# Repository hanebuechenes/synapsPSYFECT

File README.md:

# synapsPSYFECT

**synapsPSYFECT** is a high-end, 6-sheet multi-stage analog/hybrid FX Eurorack module designed for deep signal manipulation, multi-effect cross-modulation, and active spatial shaping.

The module combines a 4-Stage Vactrol Phaser, a Dual PT2399 Delay, and an LM13700-based Quadrature Frequency Shifter/Ring Modulator, all interconnected through a flexible active summing cross-modulation matrix.

---

## Technical Features & Architecture

* **Multi-Stage Architecture:** 6 dedicated schematic sheets covering Power, CV Buffering, Matrix Summing, Phaser, Dual Delay, and Frequency Shifter.
* **Active Input Buffering & Summing Matrix (`U12C`/`U4`/`U5`):** Dedicated TL074 operational amplifier buffers for all audio inputs and cross-modulation feedback paths to prevent crosstalk and signal bleed.
* **4-Stage Vactrol Phaser (`U7`/`U6`, `U8`, `U10`, `U11`):** All-pass filter architecture utilizing VTL5C vactrols for smooth, organic, analog phase shifting with CV control (`PHASER_CV`) and manual resonance feedback (`RES_POT1`).
* **Dual PT2399 Delay (`U12`/`U13`):** Two PT2399 ICs with voltage-controlled delay time (`DELAY_TIME_CV` via `Q2`/`Q3`) and transistor-shunt feedback modulation (`FEEDBACK_CV` via `Q4`).
* **LM13700 Frequency Shifter (`U14`/`U5`/`U9`):** Quadrature carrier oscillator generating sine/cosine phases (`CARRIER_SIN`/`CARRIER_COS`) driving a dual-OTA LM13700 for true frequency shifting and ring modulation (`SHIFT_CV`).
* **BOM & Component Standards:** SMD implementation (0603 / 0805 passives). **Strictly 0% Tantalum capacitors**, relying on NP0/C0G MLCCs for frequency-critical audio paths, X7R/X5R MLCCs, and SMD Aluminum Electrolytic capacitors for power rail filter banks.

---

## Module Specifications

| Specification | Parameter / Value |
| :--- | :--- |
| **Format** | Eurorack Synthesis Module |
| **Power Supply** | $\pm 12\text{VDC}$ Eurorack Standard Bus |
| **Internal Rails** | $+12\text{VA}$, $-12\text{VA}$, $+5\text{V}$, $+3.3\text{V}$, $+1.65\text{V\_REF}$ |
| **Input CV Protection** | $100\text{k}\Omega$ series resistors with 1N4148W clamping diodes & TL074 buffer stages |
| **Passive Component Sizes** | SMD 0603 (resistors & decoupling), SMD 0805 / 1206 (capacitors) |
| **IC Footprints** | SOIC-14, SOP-16, SOIC-16, SOT-223 |

---

## Signal Flow Overview

```
                          +------------------------+
                          |  CV Inputs (Protected) |
                          +-----------+------------+
                                      |
                                      v
  [AUDIO_IN] ---> [Input Buffer] ---> ( Matrix / Routing ) ---> [Phaser Stage (VTL5C)]
                       |                     |             ---> [Dual PT2399 Delay]
                       |                     |             ---> [LM13700 Freq Shifter]
                       v                     v
                 +-------------------------------+
                 | Active Cross-Mod Summing      | ---> [Audio Output]
                 | & Dry/Wet Mix (TL074)         |
                 +-------------------------------+
```

---

## Procurement & Assembly Notes

* **Capacitor Types:** 
  * Use **NP0/C0G** dielectrics for $10\text{nF}$ capacitors in the Phaser (`C13`–`C16`) and Quadrature Oscillator (`C35`–`C36`) to minimize temperature drift and microphonics.
  * Use **X7R/X5R** for all $100\text{nF}$ decoupling capacitors (`C39`–`C48` placed directly at TL074 power pins 4 & 11).
* **SMD Hand-Soldering:** 0603/0805 components chosen for manageable DIY manual assembly or automated SMT placement (JLCPCB compatible).

---

## Repository Structure

```
├── hardware/              # KiCad project files (.kicad_pro, .kicad_sch, .kicad_pcb)
├── bom/                   # Bill of Materials (BOM exports / iBOM)
├── docs/                  # Gerber files, schematic PDFs, and design notes
├── .gitignore             # KiCad temporary & build file exclusions
└── README.md              # Project documentation
```

---

## License

Hardware open-source project created by **hanebuechenes / synaps**. Distributed under the CERN-OHL-P (Permissive) or MIT License.

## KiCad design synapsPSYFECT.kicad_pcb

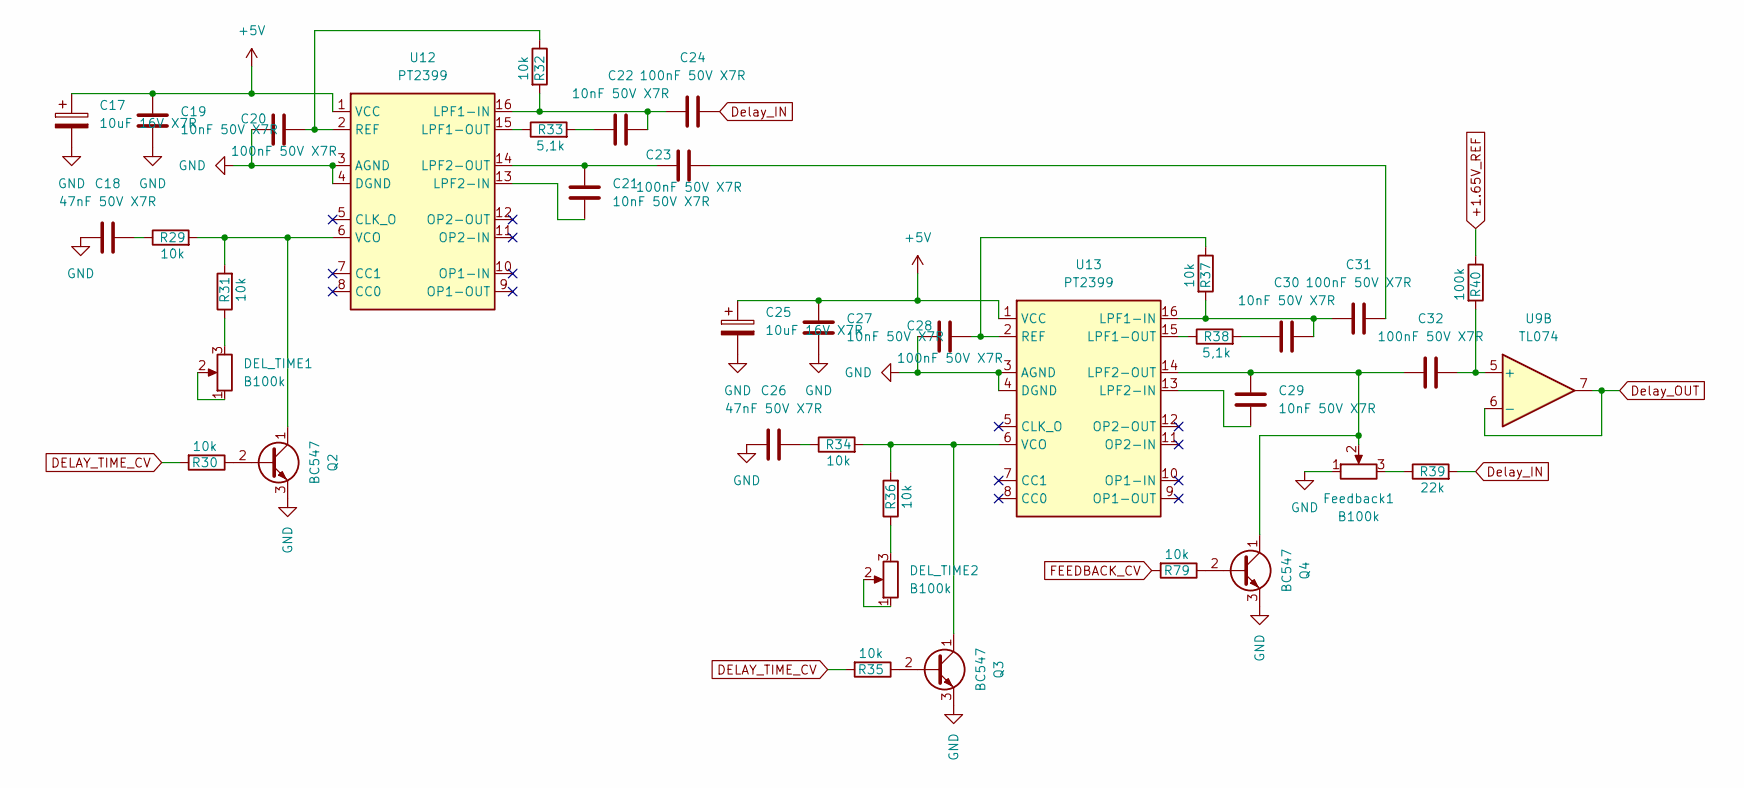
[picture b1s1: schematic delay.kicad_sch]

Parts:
C17, C25: 10uF 16V X7R; C_0805_2012Metric_Pad1.18x1.45mm_HandSolder
C18, C26: 47nF 50V X7R; C_0603_1608Metric_Pad1.08x0.95mm_HandSolder
C19, C21, C22, C27, C29, C30: 10nF 50V X7R; C_0603_1608Metric_Pad1.08x0.95mm_HandSolder
C20, C23, C24, C28, C31, C32: 100nF 50V X7R; C_0603_1608Metric_Pad1.08x0.95mm_HandSolder
DEL_TIME1, DEL_TIME2: B100k; Potentiometer_Alps_RK09K_Single_Vertical
Feedback1: B100k; Potentiometer_Alps_RK09K_Single_Vertical
Q2, Q3, Q4: BC547; SOT-23-3
R29, R30, R31, R32, R34, R35, R36, R37, R79: 10k; R_0603_1608Metric_Pad0.98x0.95mm_HandSolder
R33, R38: 5,1k; R_0603_1608Metric_Pad0.98x0.95mm_HandSolder
R39: 22k; R_0603_1608Metric_Pad0.98x0.95mm_HandSolder
R40: 100k; R_0603_1608Metric_Pad0.98x0.95mm_HandSolder
U9: TL074; SOIC-14_3.9x8.7mm_P1.27mm
U12, U13: PT2399; SOP-16_4.4x10.4mm_P1.27mm

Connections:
+1.65V_REF: R40.1; also elsewhere on the board
+5V: C17.1, C19.2, C25.1, C27.2, U12.1 (VCC), U13.1 (VCC); also elsewhere on the board
DELAY_TIME_CV: R30.2, R35.2; also elsewhere on the board
Delay_IN: C24.1, R39.2; also elsewhere on the board
Delay_OUT: U9.6 (-), U9.7; also elsewhere on the board
FEEDBACK_CV: R79.2; also elsewhere on the board
GND: C17.2, C18.1, C19.1, C20.1, C25.2, C26.1, C27.1, C28.1, Feedback1.1, Q2.3 (E), Q3.3 (E), Q4.3 (E), U12.3 (AGND), U12.4 (DGND), U13.3 (AGND), U13.4 (DGND); also elsewhere on the board
unnamed: C18.2, R29.1
unnamed: C22.1, R33.2
unnamed: C23.2, C31.1
unnamed: C26.2, R34.1
unnamed: C30.1, R38.2
unnamed: DEL_TIME1.1, DEL_TIME1.2
unnamed: DEL_TIME1.3, R31.1
unnamed: DEL_TIME2.1, DEL_TIME2.2
unnamed: DEL_TIME2.3, R36.1
unnamed: Feedback1.3, R39.1
unnamed: Q2.2 (B), R30.1
unnamed: Q2.1 (C), R29.2, R31.2, U12.6 (VCO)
unnamed: Q3.2 (B), R35.1
unnamed: Q3.1 (C), R34.2, R36.2, U13.6 (VCO)
unnamed: Q4.2 (B), R79.1
unnamed: C29.2, C32.2, Feedback1.2, Q4.1 (C), U13.14 (LPF2-OUT)
unnamed: C32.1, R40.2, U9.5 (+)
unnamed: C22.2, C24.2, R32.2, U12.16 (LPF1-IN)
unnamed: R33.1, U12.15 (LPF1-OUT)
unnamed: C21.1, U12.13 (LPF2-IN)
unnamed: C21.2, C23.1, U12.14 (LPF2-OUT)
unnamed: C20.2, R32.1, U12.2 (REF)
unnamed: C30.2, C31.2, R37.2, U13.16 (LPF1-IN)
unnamed: R38.1, U13.15 (LPF1-OUT)
unnamed: C29.1, U13.13 (LPF2-IN)
unnamed: C28.2, R37.1, U13.2 (REF)

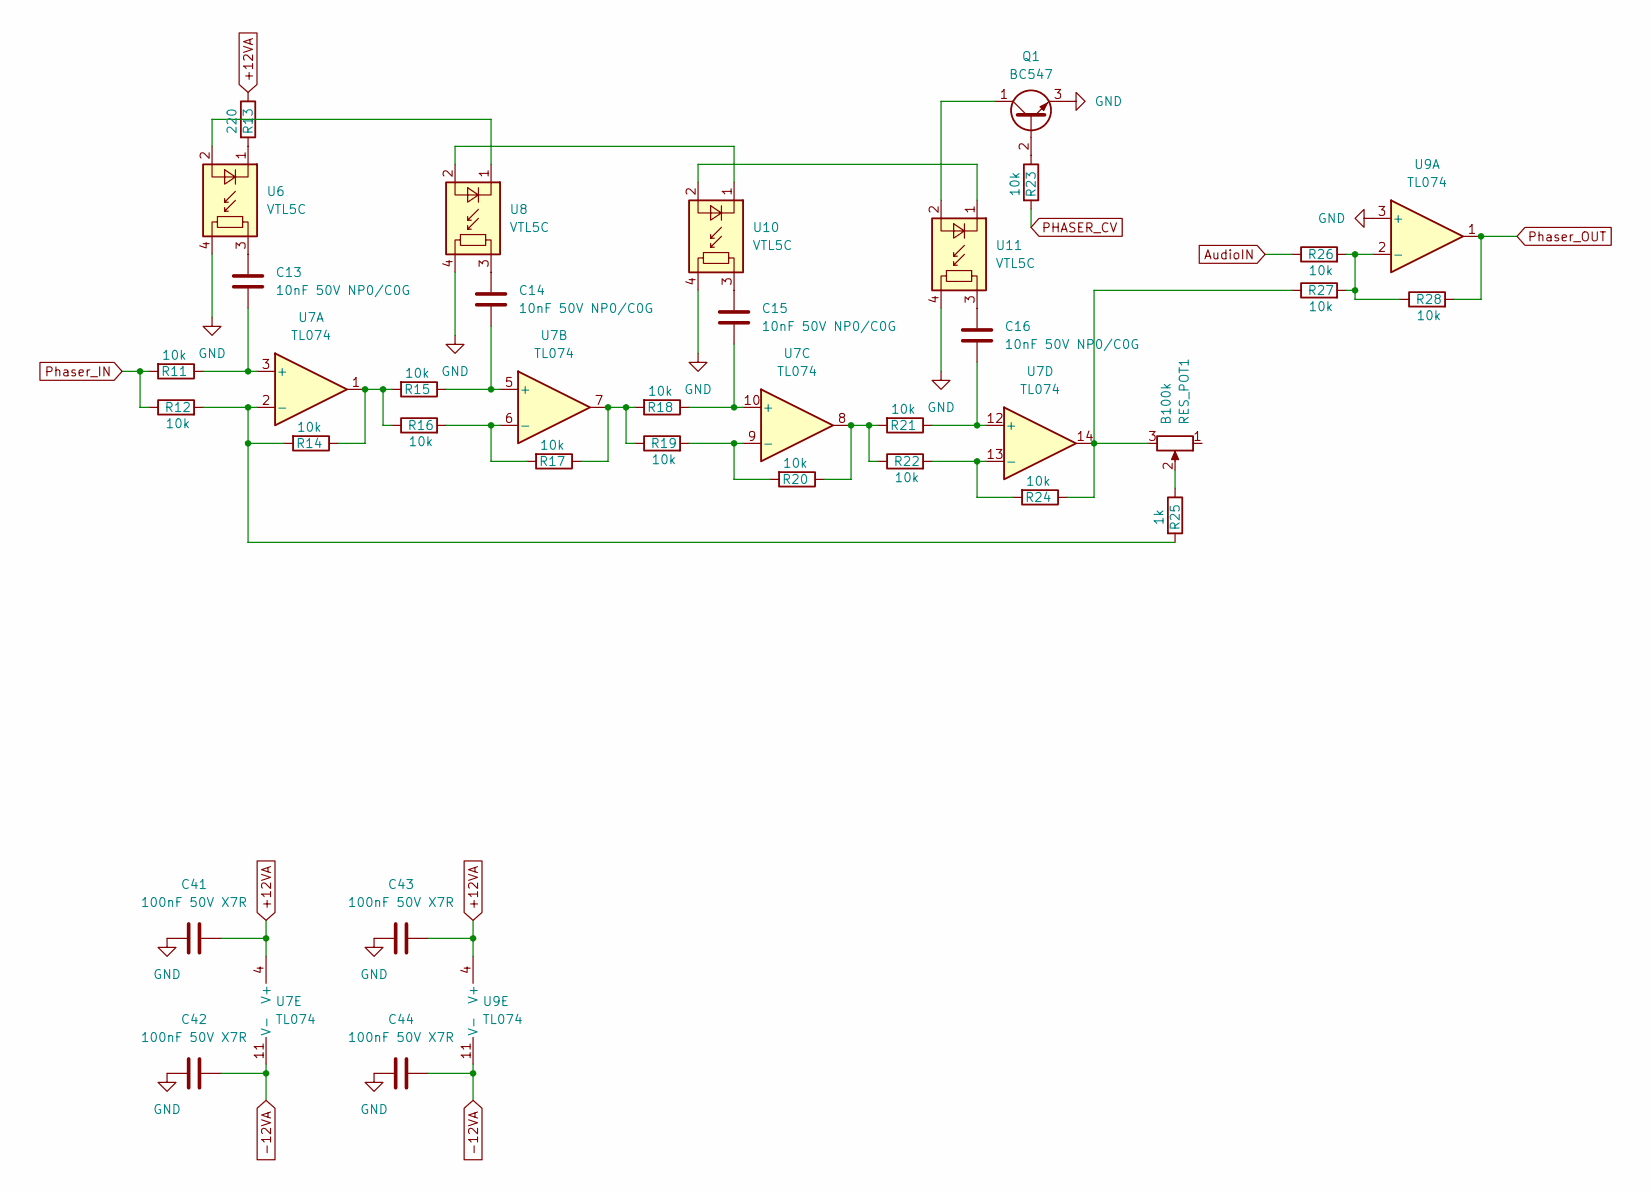
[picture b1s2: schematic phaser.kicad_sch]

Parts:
C13, C14, C15, C16: 10nF 50V NP0/C0G; C_0603_1608Metric_Pad1.08x0.95mm_HandSolder
C41, C42, C43, C44: 100nF 50V X7R; C_0603_1608Metric_Pad1.08x0.95mm_HandSolder
Q1: BC547; SOT-23-3
R11, R12, R14, R15, R16, R17, R18, R19, R20, R21, R22, R23, R24, R26, R27, R28: 10k; R_0603_1608Metric_Pad0.98x0.95mm_HandSolder
R13: 220; R_0603_1608Metric_Pad0.98x0.95mm_HandSolder
R25: 1k; R_0603_1608Metric_Pad0.98x0.95mm_HandSolder
RES_POT1: B100k; Potentiometer_Alps_RK09K_Single_Vertical
U6, U8, U10, U11: VTL5C; PerkinElmer_VTL5C
U7, U9: TL074; SOIC-14_3.9x8.7mm_P1.27mm

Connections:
+12VA: C41.2, C43.2, R13.1, U7.4 (V+), U9.4 (V+); also elsewhere on the board
-12VA: C42.2, C44.2, U7.11 (V-), U9.11 (V-); also elsewhere on the board
AudioIN: R26.1
GND: C41.1, C42.1, C43.1, C44.1, Q1.3 (E), U6.4, U8.4, U9.3 (+), U10.4, U11.4; also elsewhere on the board
unnamed: C13.1, U6.3
unnamed: C14.1, U8.3
unnamed: C15.1, U10.3
unnamed: C16.1, U11.3
unnamed: Q1.2 (B), R23.1
unnamed: Q1.1 (C), U11.2 (+)
unnamed: R14.1, R15.2, R16.1, U7.1
unnamed: R17.1, R18.2, R19.1, U7.7
unnamed: R20.1, R21.2, R22.1, U7.8
unnamed: R24.1, R27.1, RES_POT1.3, U7.14
unnamed: R25.1, RES_POT1.2
unnamed: U6.2 (+), U8.1 (-)
unnamed: R13.2, U6.1 (-)
unnamed: C13.2, R11.1, U7.3 (+)
unnamed: R12.2, R14.2, R25.2, U7.2 (-)
unnamed: C14.2, R15.1, U7.5 (+)
unnamed: R16.2, R17.2, U7.6 (-)
unnamed: C15.2, R18.1, U7.10 (+)
unnamed: R19.2, R20.2, U7.9 (-)
unnamed: C16.2, R21.1, U7.12 (+)
unnamed: R22.2, R24.2, U7.13 (-)
unnamed: R26.2, R27.2, R28.1, U9.2 (-)
unnamed: U10.2 (+), U11.1 (-)
unnamed: U8.2 (+), U10.1 (-)
PHASER_CV: R23.2; also elsewhere on the board
Phaser_IN: R11.2, R12.1; also elsewhere on the board
Phaser_OUT: R28.2, U9.1; also elsewhere on the board

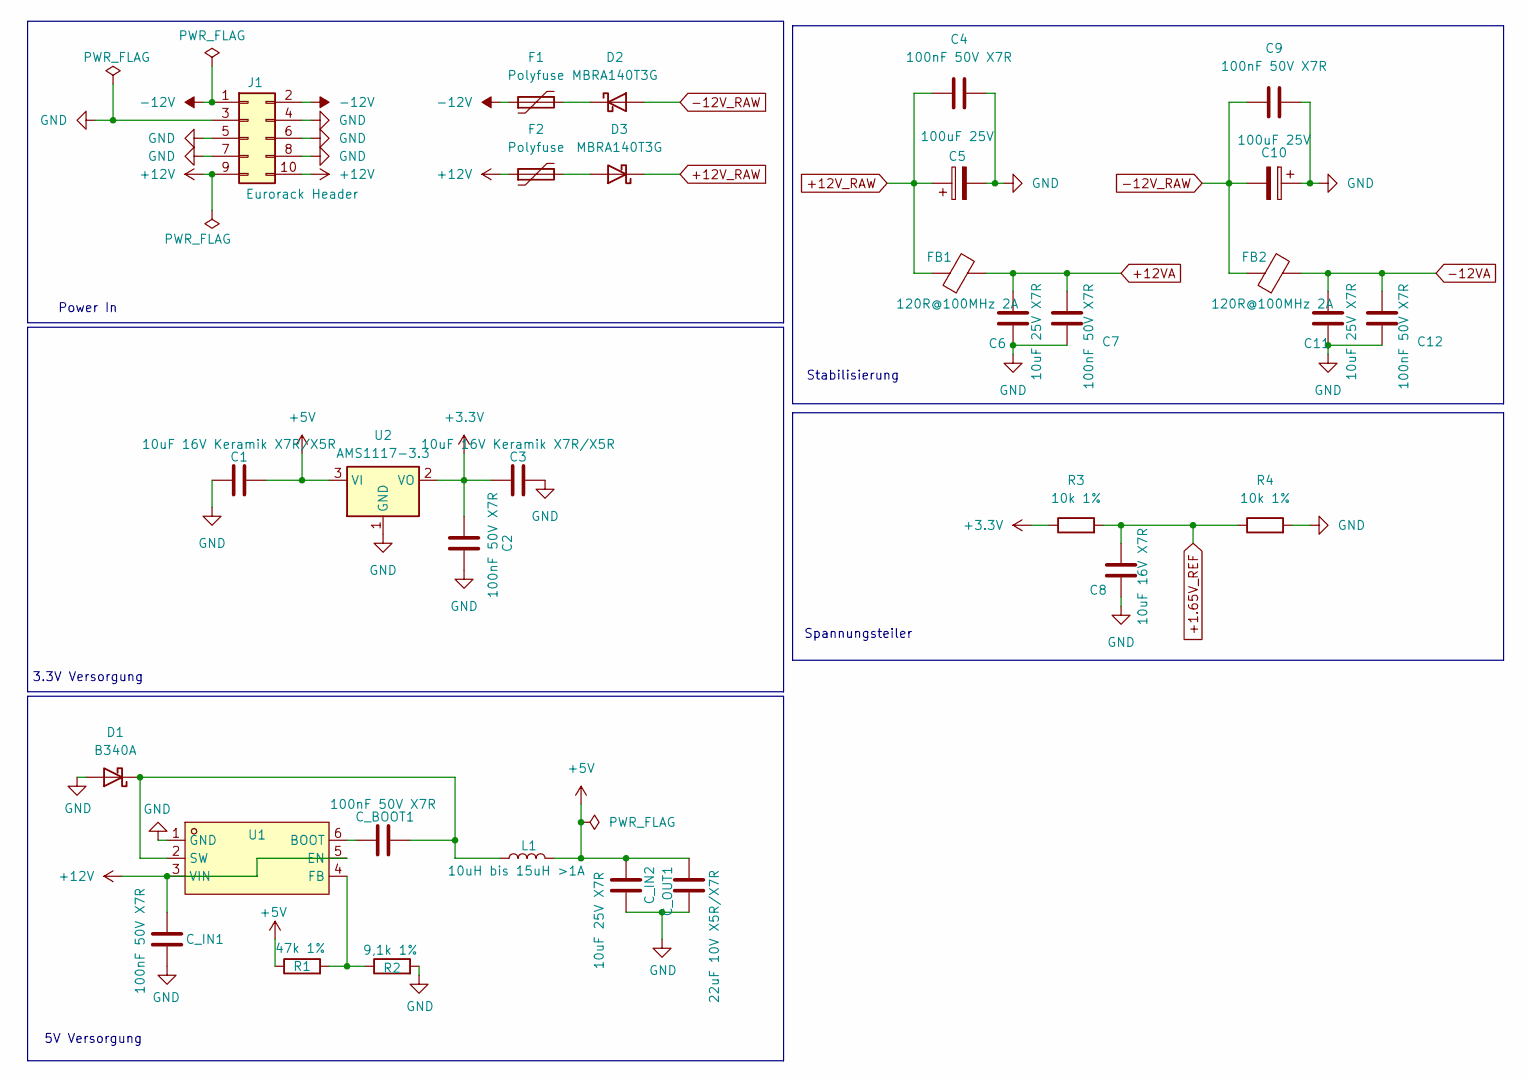
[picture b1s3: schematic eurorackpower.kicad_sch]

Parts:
C1, C3: 10uF 16V Keramik X7R/X5R; C_0805_2012Metric_Pad1.18x1.45mm_HandSolder
C2, C4, C7, C9, C12: 100nF 50V X7R; C_0603_1608Metric_Pad1.08x0.95mm_HandSolder
C5, C10: 100uF 25V; CP_Elec_6.3x7.7
C6, C11: 10uF 25V X7R; C_0805_2012Metric_Pad1.18x1.45mm_HandSolder
C8: 10uF 16V X7R; C_0805_2012Metric_Pad1.18x1.45mm_HandSolder
C_BOOT1: 100nF 50V X7R; C_0603_1608Metric_Pad1.08x0.95mm_HandSolder
C_IN1: 100nF 50V X7R; C_0603_1608Metric_Pad1.08x0.95mm_HandSolder
C_IN2: 10uF 25V X7R; C_0805_2012Metric_Pad1.18x1.45mm_HandSolder
C_OUT1: 22uF 10V X5R/X7R; C_0805_2012Metric_Pad1.18x1.45mm_HandSolder
D1: B340A; D_SMC
D2, D3: MBRA140T3G; D_SMA-SMB_Universal_Handsoldering
F1, F2: Polyfuse; Fuse_1210_3225Metric
FB1, FB2: 120R@100MHz 2A; L_0603_1608Metric_Pad1.05x0.95mm_HandSolder
J1: Eurorack Header; PinHeader_2x05_P2.54mm_Vertical
L1: 10uH bis 15uH >1A; L_Coilcraft_XxL4030
R1: 47k 1%; R_0603_1608Metric_Pad0.98x0.95mm_HandSolder
R2: 9,1k 1%; R_0603_1608Metric_Pad0.98x0.95mm_HandSolder
R3, R4: 10k 1%; R_0603_1608Metric_Pad0.98x0.95mm_HandSolder
U1: TPS54302DDCR_C311983; SOT-23-6_L2.9-W1.6-P0.95-LS2.8-BL; MPN TPS54302DDCR; LCSC Part C311983
U2: AMS1117-3.3; SOT-223-3_TabPin2

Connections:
+1.65V_REF: C8.1, R3.2, R4.1; also elsewhere on the board
+3.3V: C2.1, C3.2, R3.1, U2.2 (VO)
+5V: C1.1, C_IN2.1, C_OUT1.1, L1.2, R1.1, U2.3 (VI); also elsewhere on the board
+12V: C_IN1.1, F2.1, J1.9, J1.10, U1.3 (VIN), U1.5 (EN)
+12VA: C6.1, C7.1, FB1.2; also elsewhere on the board
+12V_RAW: C4.1, C5.1, D3.1 (K), FB1.1
-12V: F1.1, J1.1, J1.2
-12VA: C11.1, C12.1, FB2.2; also elsewhere on the board
-12V_RAW: C9.1, C10.2, D2.2 (A), FB2.1
GND: C1.2, C2.2, C3.1, C4.2, C5.2, C6.2, C7.2, C8.2, C9.2, C10.1, C11.2, C12.2, C_IN1.2, C_IN2.2, C_OUT1.2, D1.2 (A), J1.3, J1.4, J1.5, J1.6, J1.7, J1.8, R2.2, R4.2, U1.1 (GND), U2.1 (GND); also elsewhere on the board
unnamed: C_BOOT1.2, D1.1 (K), L1.1, U1.2 (SW)
unnamed: D2.1 (K), F1.2
unnamed: D3.2 (A), F2.2
unnamed: C_BOOT1.1, U1.6 (BOOT)
unnamed: R1.2, R2.1, U1.4 (FB)

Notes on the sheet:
5V Versorgung
Power In
Spannungsteiler
Stabilisierung
3.3V Versorgung

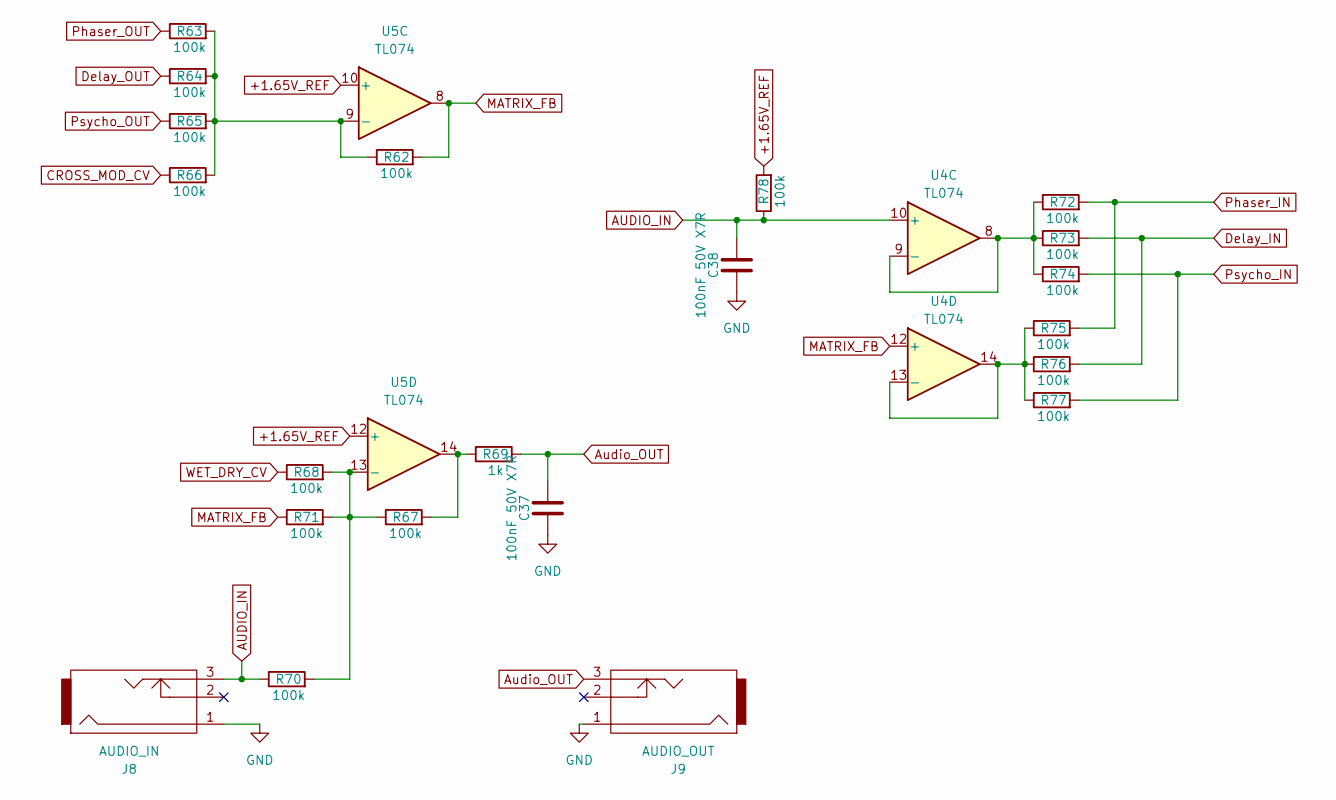
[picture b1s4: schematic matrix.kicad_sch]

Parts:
C37, C38: 100nF 50V X7R; C_0603_1608Metric_Pad1.08x0.95mm_HandSolder
J8: AUDIO_IN; PJ301M-12; MFG Part Number WQP-WQP518MA; Digikey Part Number N/A
J9: AUDIO_OUT; PJ301M-12; MFG Part Number WQP-WQP518MA; Digikey Part Number N/A
R62, R63, R64, R65, R66, R67, R68, R70, R71, R72, R73, R74, R75, R76, R77, R78: 100k; R_0603_1608Metric_Pad0.98x0.95mm_HandSolder
R69: 1k; R_0603_1608Metric_Pad0.98x0.95mm_HandSolder
U4, U5: TL074; SOIC-14_3.9x8.7mm_P1.27mm

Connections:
+1.65V_REF: R78.2, U5.10 (+), U5.12 (+); also elsewhere on the board
AUDIO_IN: C38.1, J8.3, R70.1, R78.1, U4.10 (+)
Audio_OUT: C37.1, J9.3, R69.2
CROSS_MOD_CV: R66.1; also elsewhere on the board
Delay_IN: R73.2, R76.2; also elsewhere on the board
Delay_OUT: R64.1; also elsewhere on the board
GND: C37.2, C38.2, J8.1, J9.1; also elsewhere on the board
MATRIX_FB: R62.2, R71.1, U4.12 (+), U5.8
unnamed: R67.2, R69.1, U5.14
unnamed: R72.1, R73.1, R74.1, U4.8, U4.9 (-)
unnamed: R75.1, R76.1, R77.1, U4.13 (-), U4.14
unnamed: R62.1, R63.2, R64.2, R65.2, R66.2, U5.9 (-)
unnamed: R67.1, R68.2, R70.2, R71.2, U5.13 (-)
Phaser_IN: R72.2, R75.2; also elsewhere on the board
Phaser_OUT: R63.1; also elsewhere on the board
Psycho_IN: R74.2, R77.2; also elsewhere on the board
Psycho_OUT: R65.1; also elsewhere on the board
WET_DRY_CV: R68.1; also elsewhere on the board

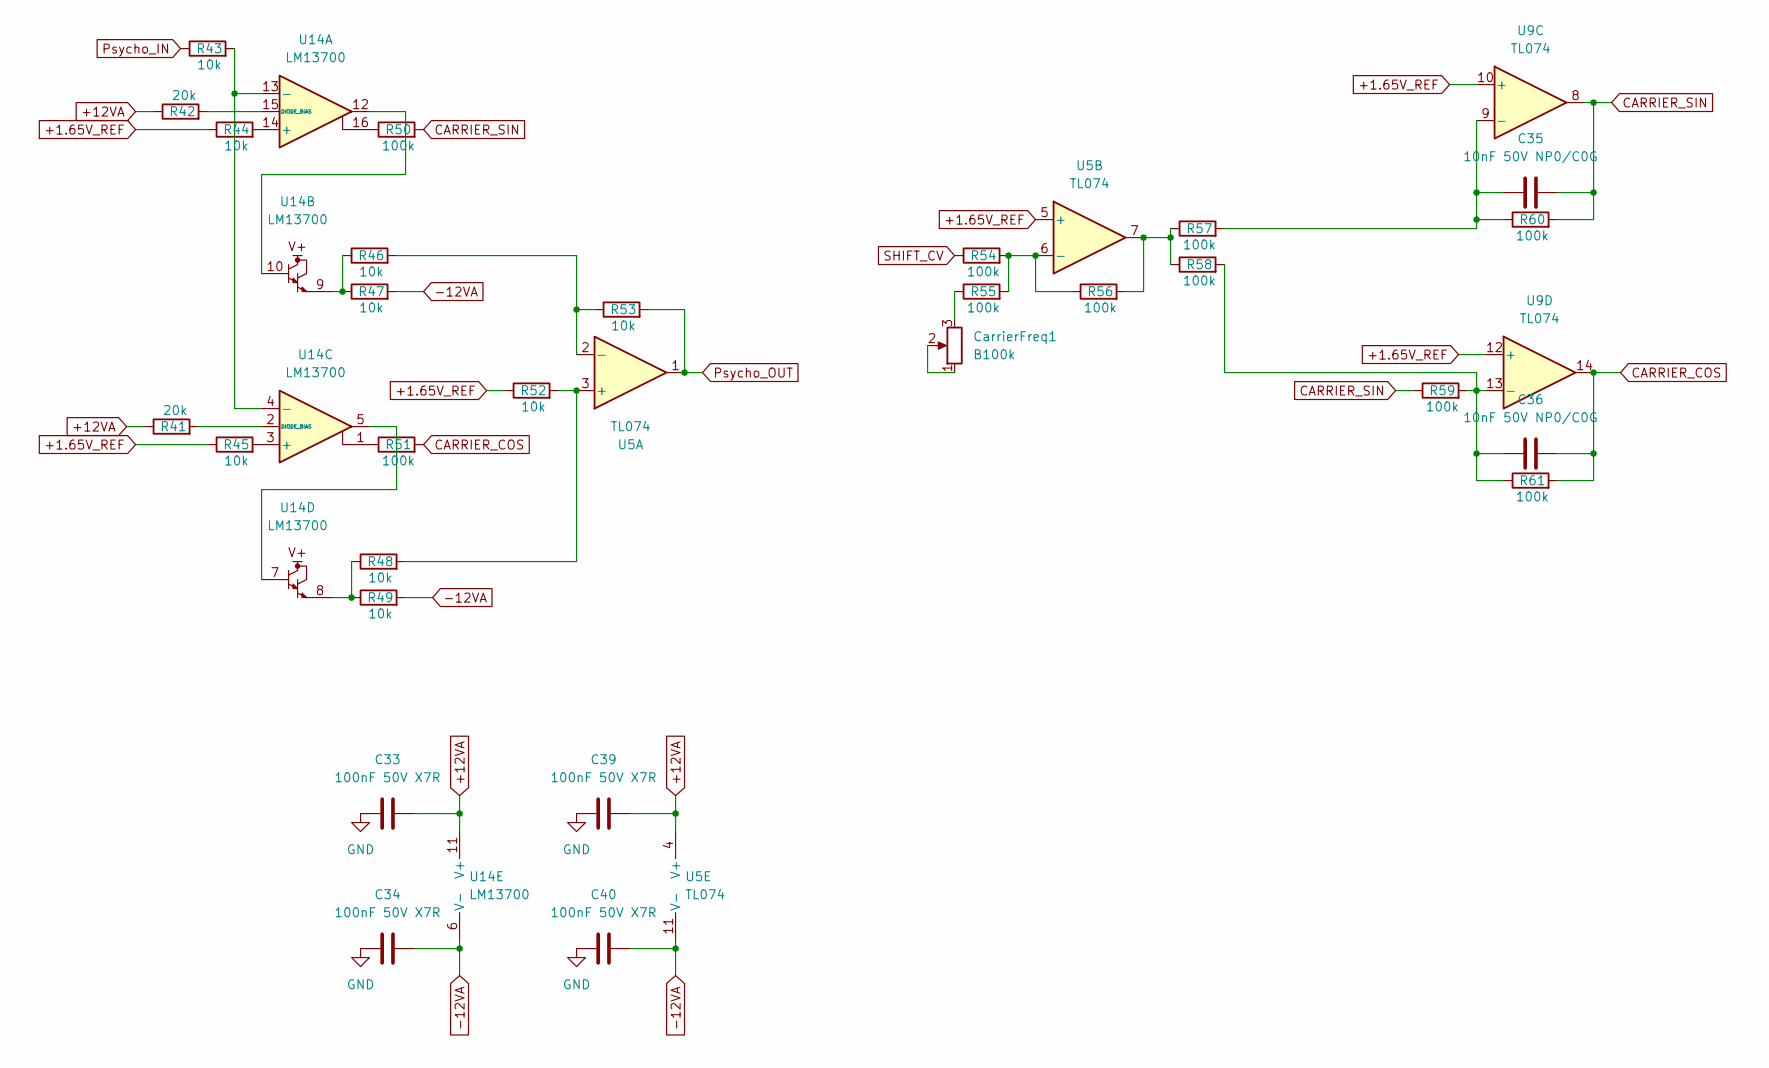
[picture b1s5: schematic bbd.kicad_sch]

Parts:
C33, C34, C39, C40: 100nF 50V X7R; C_0603_1608Metric_Pad1.08x0.95mm_HandSolder
C35, C36: 10nF 50V NP0/C0G; C_0603_1608Metric_Pad1.08x0.95mm_HandSolder
CarrierFreq1: B100k; Potentiometer_Alps_RK09K_Single_Vertical
R41, R42: 20k; R_0603_1608Metric_Pad0.98x0.95mm_HandSolder
R43, R44, R45, R46, R47, R48, R49, R52, R53: 10k; R_0603_1608Metric_Pad0.98x0.95mm_HandSolder
R50, R51, R54, R55, R56, R57, R58, R59, R60, R61: 100k; R_0603_1608Metric_Pad0.98x0.95mm_HandSolder
U5, U9: TL074; SOIC-14_3.9x8.7mm_P1.27mm
U14: LM13700; SOIC-16_3.9x9.9mm_P1.27mm

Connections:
+1.65V_REF: R44.1, R45.1, R52.1, U5.5 (+), U9.10 (+), U9.12 (+); also elsewhere on the board
+12VA: C33.2, C39.2, R41.1, R42.1, U5.4 (V+), U14.11 (V+); also elsewhere on the board
-12VA: C34.2, C40.2, R47.2, R49.2, U5.11 (V-), U14.6 (V-); also elsewhere on the board
CARRIER_COS: C36.2, R51.2, R61.2, U9.14
CARRIER_SIN: C35.2, R50.2, R59.1, R60.2, U9.8
GND: C33.1, C34.1, C39.1, C40.1; also elsewhere on the board
unnamed: CarrierFreq1.1, CarrierFreq1.2
unnamed: CarrierFreq1.3, R55.1
unnamed: R46.1, R47.1, U14.9
unnamed: R48.1, R49.1, U14.8
unnamed: R50.1, U14.16
unnamed: R51.1, U14.1
unnamed: R56.2, R57.1, R58.1, U5.7
unnamed: R48.2, R52.2, U5.3 (+)
unnamed: R46.2, R53.1, U5.2 (-)
unnamed: R54.2, R55.2, R56.1, U5.6 (-)
unnamed: C35.1, R57.2, R60.1, U9.9 (-)
unnamed: C36.1, R58.2, R59.2, R61.1, U9.13 (-)
unnamed: U14.5, U14.7
unnamed: U14.10, U14.12
unnamed: R44.2, U14.14 (+)
unnamed: R43.2, U14.4 (-), U14.13 (-)
unnamed: R42.2, U14.15 (DIODE_BIAS)
unnamed: R45.2, U14.3 (+)
unnamed: R41.2, U14.2 (DIODE_BIAS)
Psycho_IN: R43.1; also elsewhere on the board
Psycho_OUT: R53.2, U5.1; also elsewhere on the board
SHIFT_CV: R54.1; also elsewhere on the board

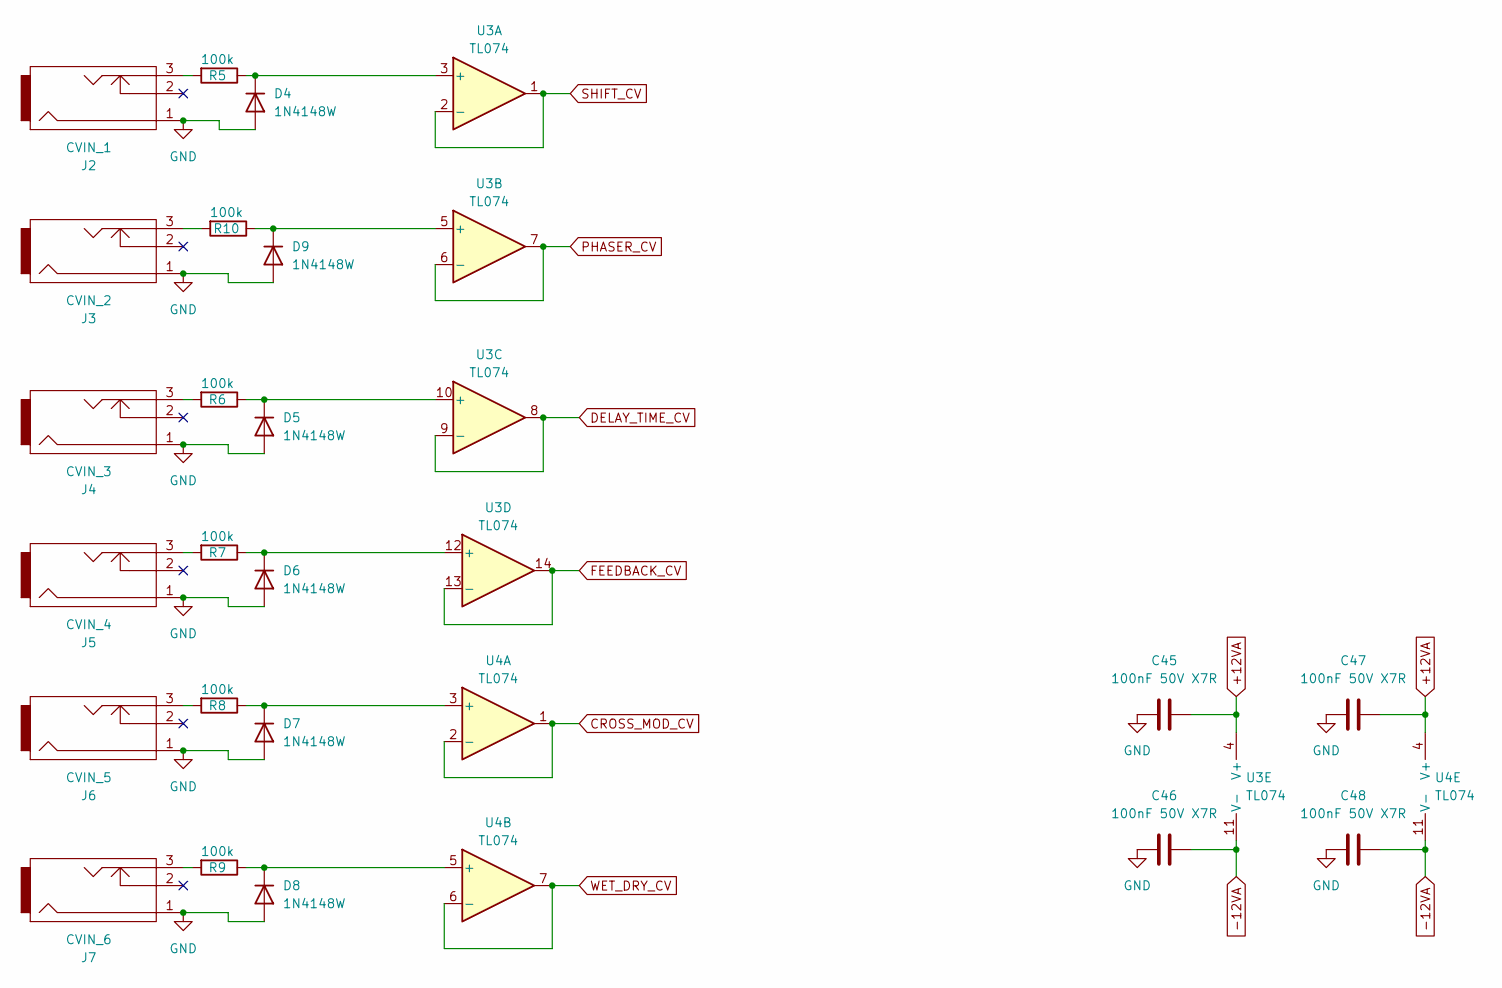
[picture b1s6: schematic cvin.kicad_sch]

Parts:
C45, C46, C47, C48: 100nF 50V X7R; C_0603_1608Metric_Pad1.08x0.95mm_HandSolder
D4, D5, D6, D7, D8, D9: 1N4148W; D_SOD-123
J2: CVIN_1; PJ301M-12; MFG Part Number WQP-WQP518MA; Digikey Part Number N/A
J3: CVIN_2; PJ301M-12; MFG Part Number WQP-WQP518MA; Digikey Part Number N/A
J4: CVIN_3; PJ301M-12; MFG Part Number WQP-WQP518MA; Digikey Part Number N/A
J5: CVIN_4; PJ301M-12; MFG Part Number WQP-WQP518MA; Digikey Part Number N/A
J6: CVIN_5; PJ301M-12; MFG Part Number WQP-WQP518MA; Digikey Part Number N/A
J7: CVIN_6; PJ301M-12; MFG Part Number WQP-WQP518MA; Digikey Part Number N/A
R5, R6, R7, R8, R9, R10: 100k; R_0603_1608Metric_Pad0.98x0.95mm_HandSolder
U3, U4: TL074; SOIC-14_3.9x8.7mm_P1.27mm

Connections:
+12VA: C45.2, C47.2, U3.4 (V+), U4.4 (V+); also elsewhere on the board
-12VA: C46.2, C48.2, U3.11 (V-), U4.11 (V-); also elsewhere on the board
CROSS_MOD_CV: U4.1, U4.2 (-); also elsewhere on the board
DELAY_TIME_CV: U3.8, U3.9 (-); also elsewhere on the board
FEEDBACK_CV: U3.13 (-), U3.14; also elsewhere on the board
GND: C45.1, C46.1, C47.1, C48.1, D4.2 (A), D5.2 (A), D6.2 (A), D7.2 (A), D8.2 (A), D9.2 (A), J2.1, J3.1, J4.1, J5.1, J6.1, J7.1; also elsewhere on the board
unnamed: D4.1 (K), R5.1, U3.3 (+)
unnamed: D5.1 (K), R6.1, U3.10 (+)
unnamed: D6.1 (K), R7.1, U3.12 (+)
unnamed: D7.1 (K), R8.1, U4.3 (+)
unnamed: D8.1 (K), R9.1, U4.5 (+)
unnamed: D9.1 (K), R10.1, U3.5 (+)
unnamed: J2.3, R5.2
unnamed: J3.3, R10.2
unnamed: J4.3, R6.2
unnamed: J5.3, R7.2
unnamed: J6.3, R8.2
unnamed: J7.3, R9.2
PHASER_CV: U3.6 (-), U3.7; also elsewhere on the board
SHIFT_CV: U3.1, U3.2 (-); also elsewhere on the board
WET_DRY_CV: U4.6 (-), U4.7; also elsewhere on the board

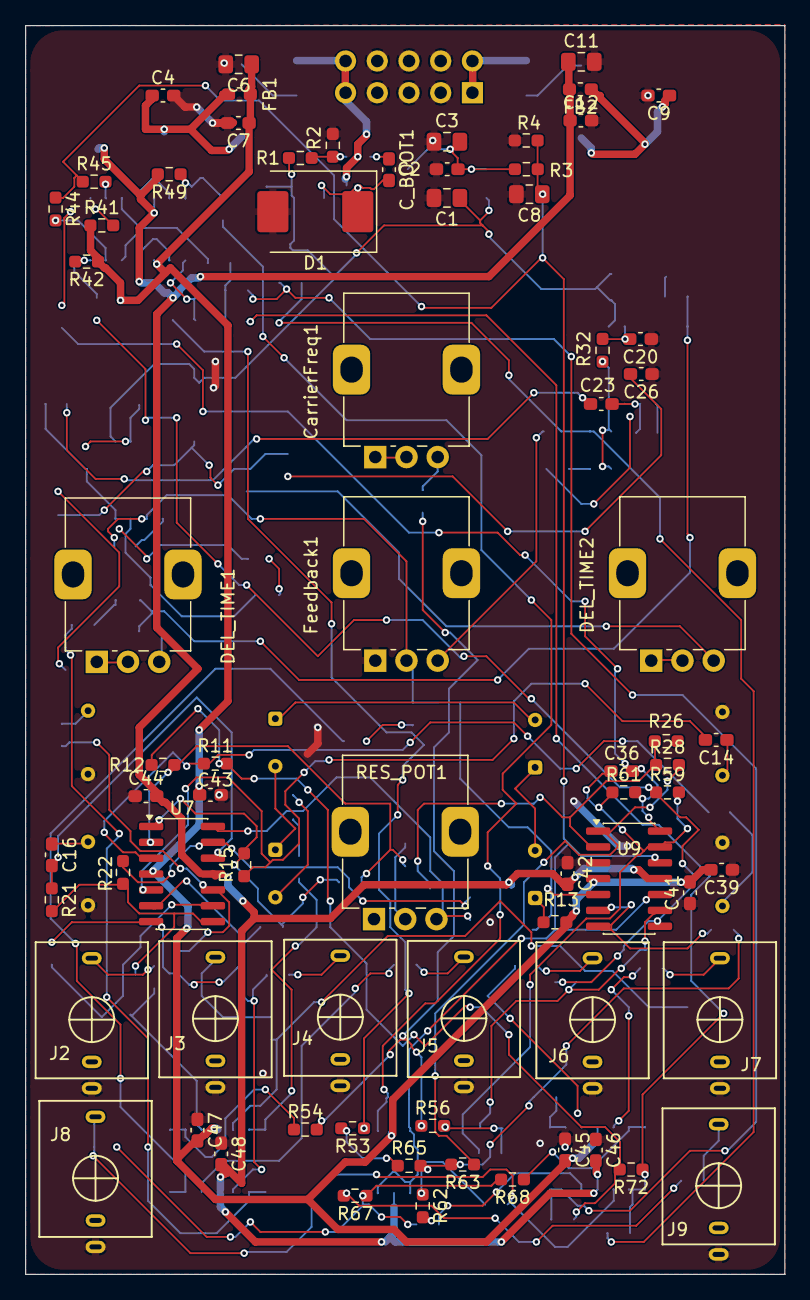
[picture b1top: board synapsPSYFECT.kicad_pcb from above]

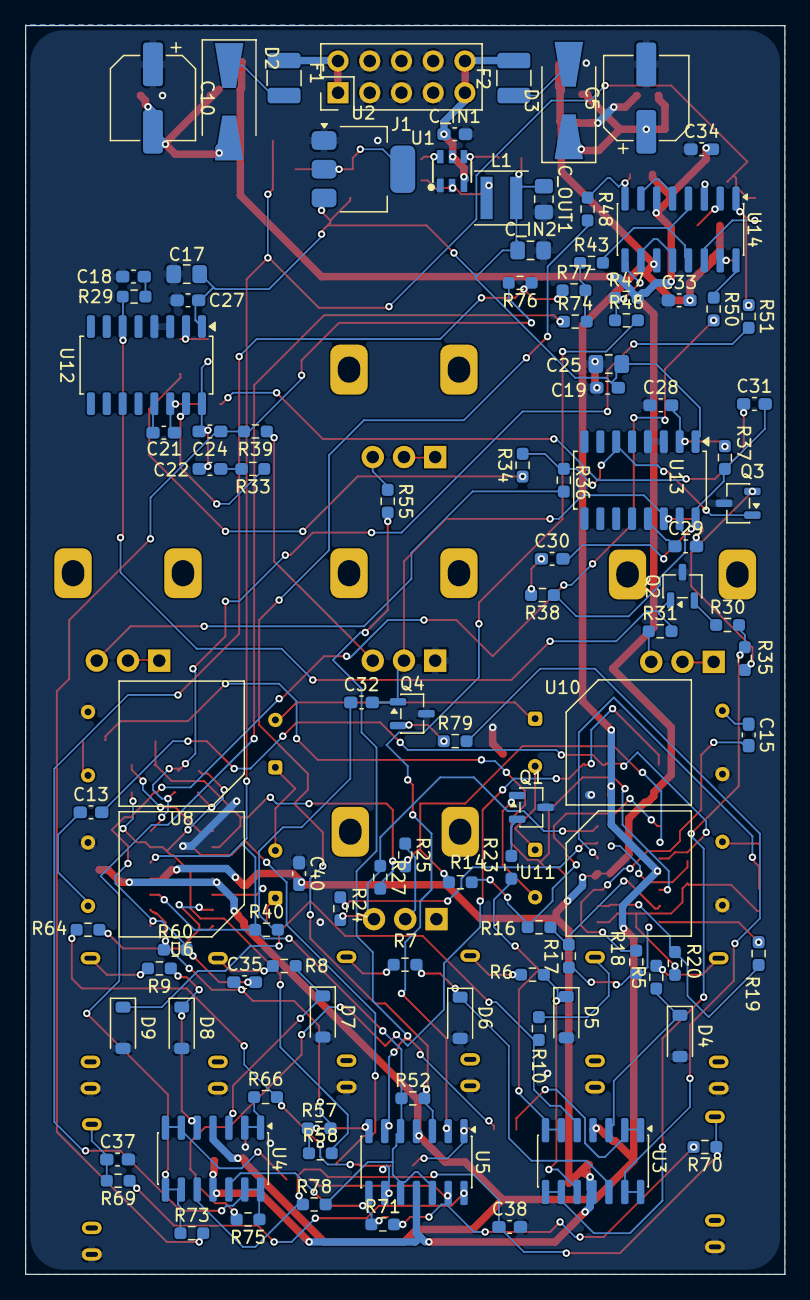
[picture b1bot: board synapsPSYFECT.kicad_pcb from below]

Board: 2 copper layers, 60.8 x 100.0 mm, 177 parts (104 on the bottom side), 118 nets.

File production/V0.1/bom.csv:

Designator,Footprint,Quantity,Value,LCSC Part #
"C1, C3",0805,2,10uF 16V Keramik X7R/X5R,
"C10, C5",CP_Elec_6.3x7.7,2,100uF 25V,
"C11, C6, C_IN2",0805,3,10uF 25V X7R,
"C12, C2, C20, C23, C24, C28, C31, C32, C33, C34, C37, C38, C39, C4, C40, C41, C42, C43, C44, C45, C46, C47, C48, C7, C9, C_BOOT1, C_IN1",0603,27,100nF 50V X7R,
"C13, C14, C15, C16, C35, C36",0603,6,10nF 50V NP0/C0G,
"C17, C25, C8",0805,3,10uF 16V X7R,
"C18, C26",0603,2,47nF 50V X7R,
"C19, C21, C22, C27, C29, C30",0603,6,10nF 50V X7R,
"CARRIERFREQ1, DEL_TIME1, DEL_TIME2, FEEDBACK1, RES_POT1",Potentiometer_Alps_RK09K_Single_Vertical,5,B100k,
C_OUT1,0805,1,22uF 10V X5R/X7R,
D1,D_SMC,1,B340A,
"D2, D3",D_SMA-SMB_Universal_Handsoldering,2,MBRA140T3G,
"D4, D5, D6, D7, D8, D9",D_SOD-123,6,1N4148W,
"F1, F2",1210,2,Polyfuse,
"FB1, FB2",0603,2,120R@100MHz 2A,
J1,PinHeader_2x05_P2.54mm_Vertical,1,Eurorack Header,
J2,PJ301M-12,1,CVIN_1,
J3,PJ301M-12,1,CVIN_2,
J4,PJ301M-12,1,CVIN_3,
J5,PJ301M-12,1,CVIN_4,
J6,PJ301M-12,1,CVIN_5,
J7,PJ301M-12,1,CVIN_6,
J8,PJ301M-12,1,AUDIO_IN,
J9,PJ301M-12,1,AUDIO_OUT,
L1,L_Coilcraft_XxL4030,1,10uH bis 15uH >1A,
"Q1, Q2, Q3, Q4",SOT-23-3,4,BC547,
R1,0603,1,47k 1%,
"R10, R40, R5, R50, R51, R54, R55, R56, R57, R58, R59, R6, R60, R61, R62, R63, R64, R65, R66, R67, R68, R7, R70, R71, R72, R73, R74, R75, R76, R77, R78, R8, R9",0603,33,100k,
"R11, R12, R14, R15, R16, R17, R18, R19, R20, R21, R22, R23, R24, R26, R27, R28, R29, R30, R31, R32, R34, R35, R36, R37, R43, R44, R45, R46, R47, R48, R49, R52, R53, R79",0603,34,10k,
R13,0603,1,220,
R2,0603,1,"9,1k 1%",
"R25, R69",0603,2,1k,
"R3, R4",0603,2,10k 1%,
"R33, R38",0603,2,"5,1k",
R39,0603,1,22k,
"R41, R42",0603,2,20k,
U1,SOT-23-6_L2.9-W1.6-P0.95-LS2.8-BL,1,TPS54302DDCR_C311983,C311983
"U10, U11, U6, U8",PerkinElmer_VTL5C,4,VTL5C,
"U12, U13",SOP-16_4.4x10.4mm_P1.27mm,2,PT2399,
U14,SOIC-16_3.9x9.9mm_P1.27mm,1,LM13700,
U2,SOT-223-3_TabPin2,1,AMS1117-3.3,
"U3, U4, U5, U7, U9",SOIC-14_3.9x8.7mm_P1.27mm,5,TL074,
